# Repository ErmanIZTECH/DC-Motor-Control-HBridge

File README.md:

# DC-Motor-Control-HBridge

Dc Motor control using Arduino PWM, H-Bridge, IR2101

## Eagle Design.

## Simulation preview

## Printed Board.

## After some decent Soldering :) 
**(_Don't worry I have improved my soldering skills._)**

## The pwm signal seen on DC motor.

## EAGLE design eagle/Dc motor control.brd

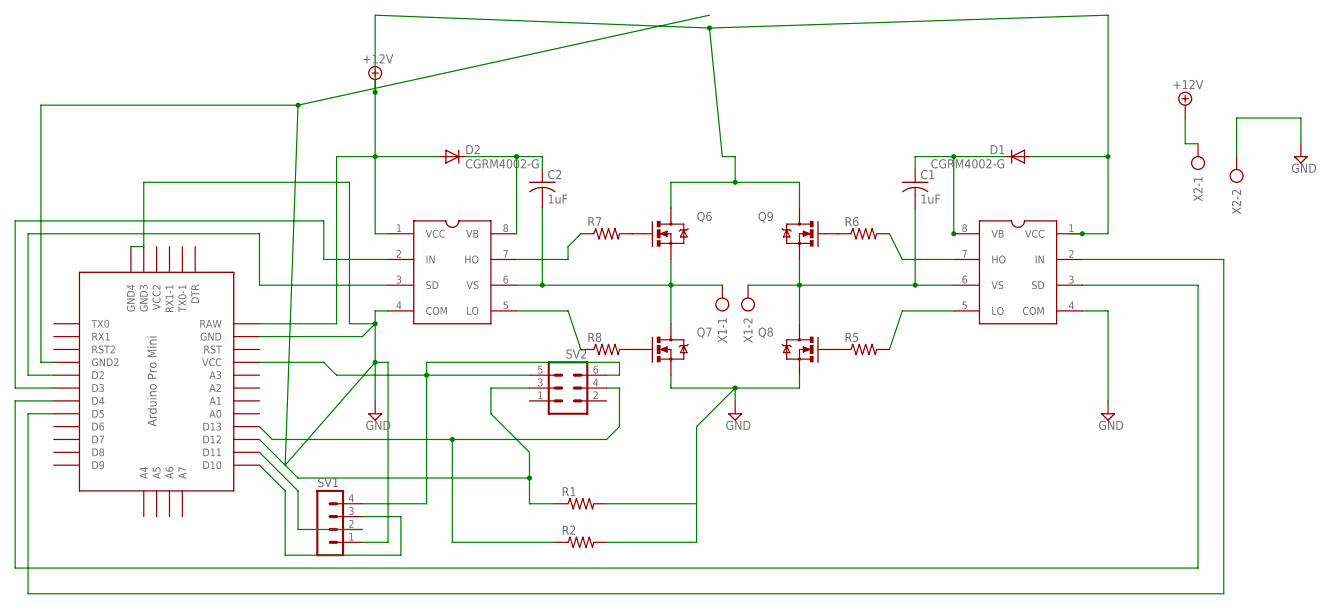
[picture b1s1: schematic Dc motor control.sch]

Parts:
C1, C2: 1uF; C1210
D1, D2: CGRM4002-G; SOD-123_MINI-SMA
Q6, Q7, Q8, Q9: MOSFET-NCHANNELFDD8580; DPAK
R1, R2, R5, R6, R7, R8: R-US_R0402; R0402
SV1: MA04-1
SV2: MA03-2
U$1, U$2: IR2104S
U$3: PRO-MINI
X1, X2: AK500/2-H

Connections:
+12V: D1.A, D2.A, Q6.4 (D), Q9.4 (D), U$1.1 (VCC), U$2.1 (VCC), U$3.RAW, X2.1
GND: Q7.3 (S), Q8.3 (S), R1.2, R2.2, SV1.1, U$1.4 (COM), U$2.4 (COM), U$3.GND, U$3.GND1 (GND2), U$3.GND2 (GND4), U$3.GND3, X2.2
unnamed: C2.2, Q6.3 (S), Q7.4 (D), U$2.6 (VS), X1.1
unnamed: C1.2, Q8.4 (D), Q9.3 (S), U$1.6 (VS), X1.2
unnamed: Q7.1 (G), R8.2
unnamed: Q6.1 (G), R7.2
unnamed: C1.1, D1.C, U$1.8 (VB)
unnamed: R7.1, U$2.7 (HO)
unnamed: R8.1, U$2.5 (LO)
unnamed: R5.2, U$1.5 (LO)
unnamed: R6.2, U$1.7 (HO)
unnamed: Q8.1 (G), R5.1
unnamed: C2.1, D2.C, U$2.8 (VB)
unnamed: Q9.1 (G), R6.1
unnamed: U$2.2 (IN), U$3.D3
unnamed: U$1.3 (SD), U$3.D4
unnamed: U$2.3 (SD), U$3.D2
unnamed: U$1.2 (IN), U$3.D5
unnamed: R2.1, SV2.4, U$3.D13
unnamed: SV1.3, U$3.D10
unnamed: SV1.4, SV2.5, SV2.6, U$3.VCC
unnamed: SV1.2, U$3.D11
unnamed: R1.1, SV2.3, U$3.D12

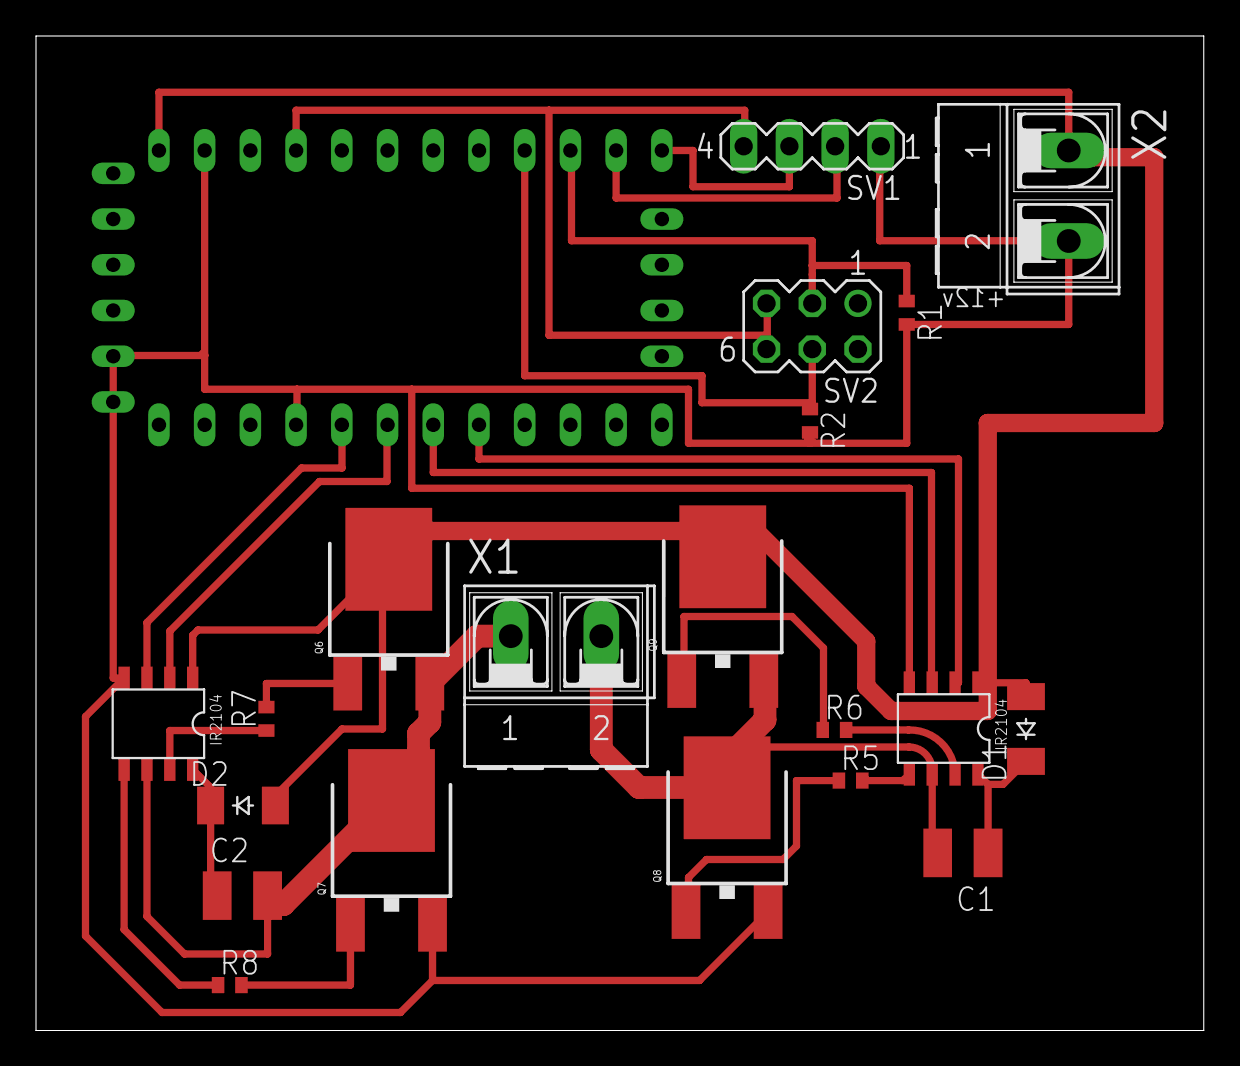
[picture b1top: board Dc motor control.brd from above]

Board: 4 copper layers, 64.9 x 55.2 mm, 21 parts (0 on the bottom side), 23 nets.

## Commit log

2017-07-30 Simulation files Proteus 8
2017-07-30 Datasheet of Mosfets
2017-07-30 Arduino code Change in your needs
2017-07-30 Photos.
2017-07-30 Added photos
2017-07-30 Eagle design screenshot
2017-07-30 Eagle Board screenshot file
2017-07-30 Proteus Screenshot
2018-08-24 high and low side driver IC
    IR2101 IC Datasheet
